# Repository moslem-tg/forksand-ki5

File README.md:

# ki5 RISC-V PCB in KiCAD

The ki5 board is a KiCAD port of SiFive's HiFive Unleashed board for the
RISC-V processor.

First draft done for:

* Ethernet
* FMC Connector
* Power Supply
* USB to UART and JTAG
* Freedom U540 IO and Power
* DDR 4x8 32 bits
* DDR 4x8 32 bit and ECC
* Freedom U540 DDR and Chiplink
* First draft of the Board

It remains to finish and check power circuits for this list.

The second draft, release of the Board in progress.

(C) 2018, 2019, Fork Sand, Inc.

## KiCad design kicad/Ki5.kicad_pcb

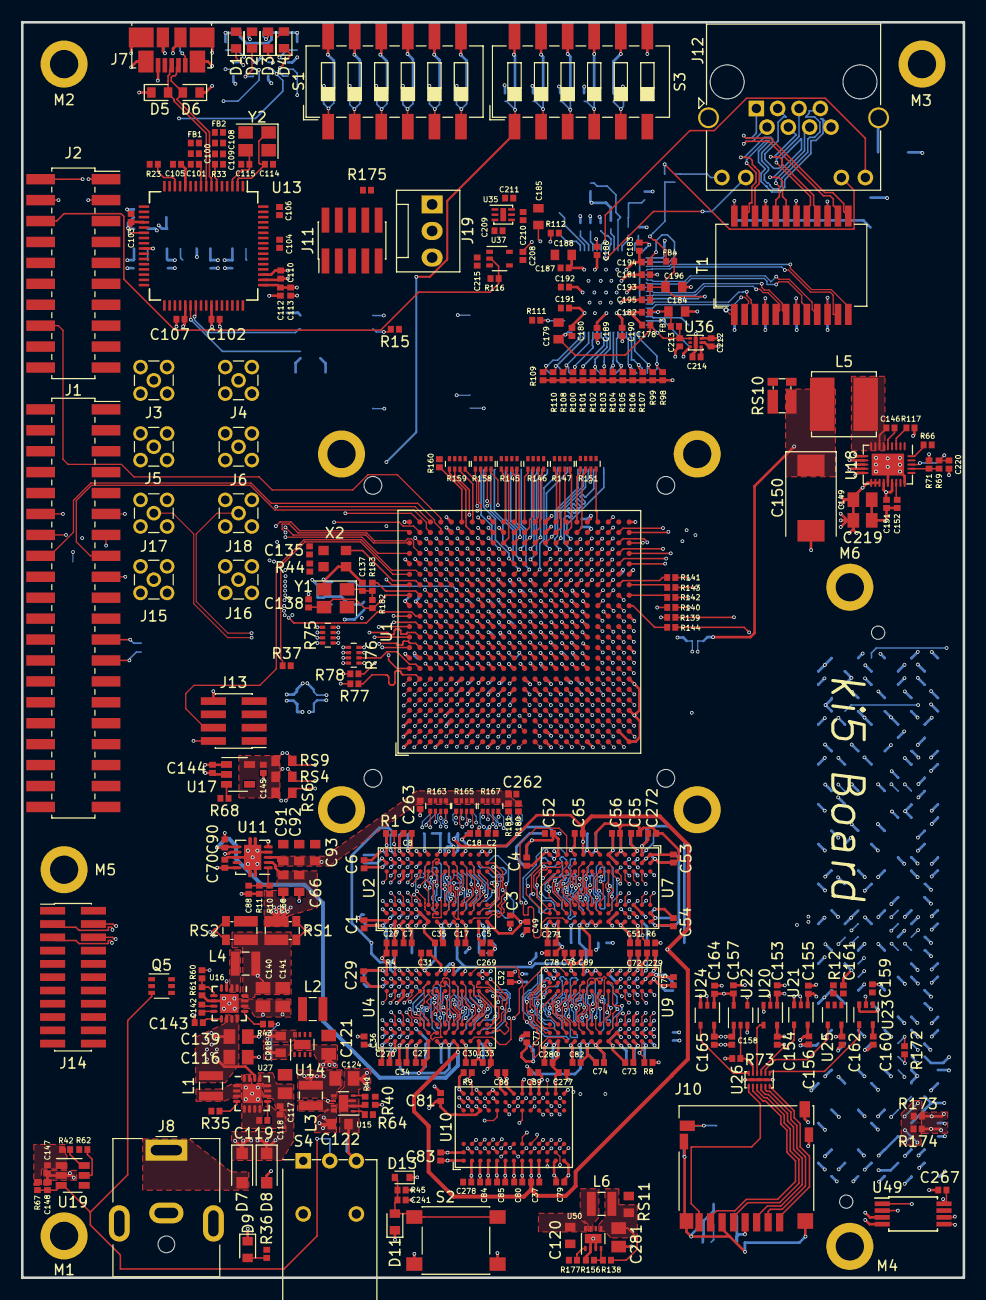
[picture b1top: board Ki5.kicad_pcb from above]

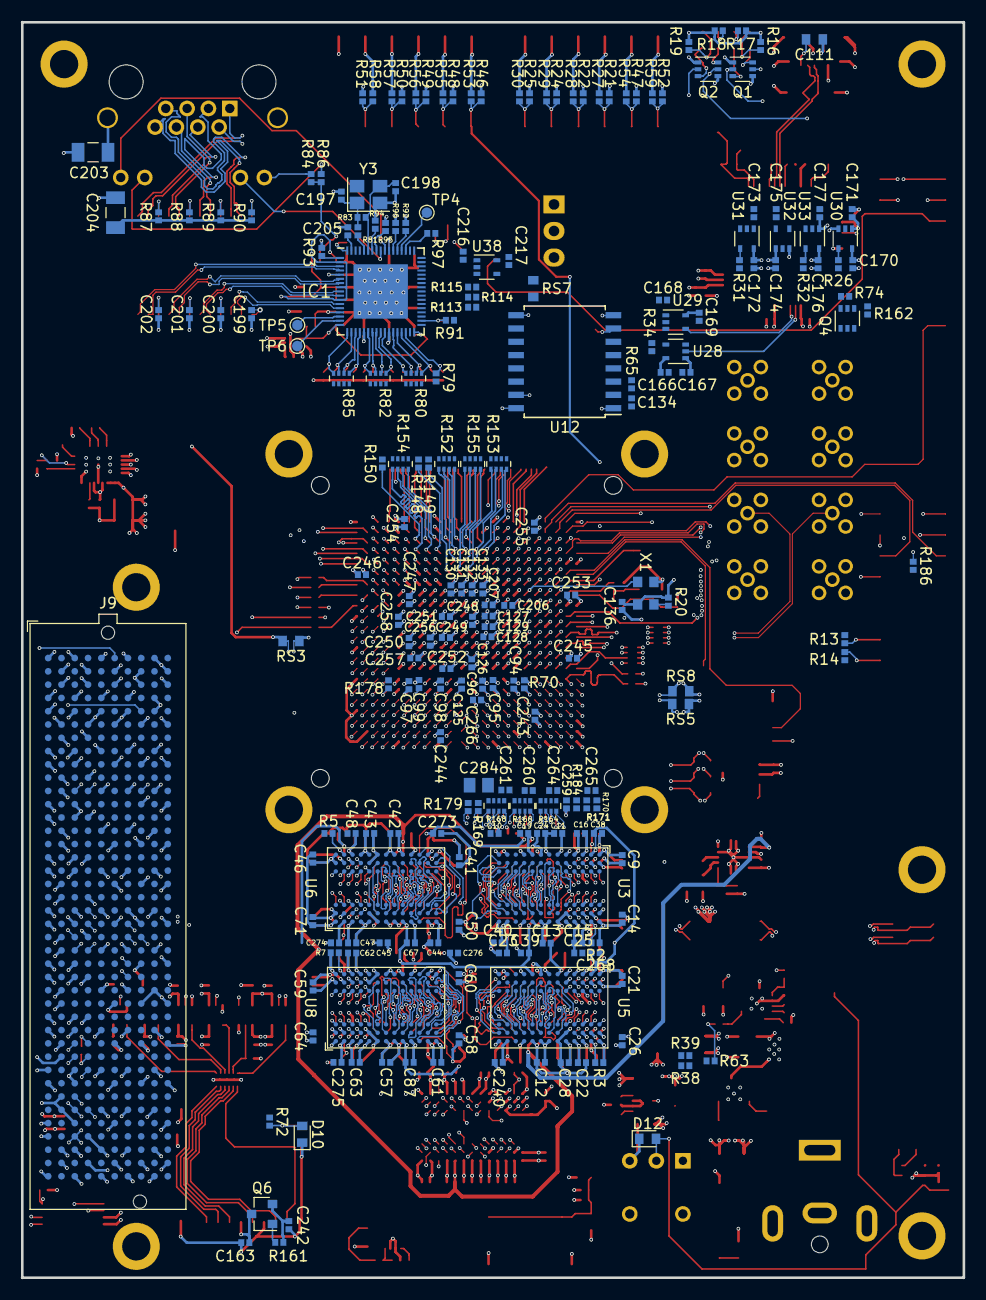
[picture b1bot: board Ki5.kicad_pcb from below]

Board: 10 copper layers, 90.0 x 120.0 mm, 542 parts (227 on the bottom side), 569 nets.

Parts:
C1, C6, C9, C14, C21, C26, C29, C34, C41, C46, C49, C54, C57, C62, C70, C71, C76, C79, C84, C94, C95, C96, C97, C100, C108, C112, C130, C131, C151, C163, C213, C243, C244, C245, C246, C247, C248, C249, C250, C251, C252: 4.7uF; C_0402_1005Metric
C2, C3, C4, C5, C7, C8, C10, C11, C12, C13, C15, C16, C17, C19, C22, C23, C24, C25, C27, C28, C30, C31, C32, C33, C35, C36, C37, C39, C42, C43, C44, C45, C47, C48, C50, C51, C52, C53, C55, C56, C58, C59, C60, C61, C63, C64, C65, C67, C69, C72, C73, C74, C75, C77, C78, C80, C81, C82, C83, C85, C86, C87, C89, C90, C98, C99, C101, C102, C103, C104, C105, C106, C107, C109, C110, C113, C118, C125, C126, C127, C129, C132, C133, C134, C135, C136, C146, C147, C153, C154, C155, C156, C157, C158, C159, C160, C161, C162, C164, C165, C166, C167, C168, C169, C170, C171, C172, C173, C174, C175, C176, C177, C178, C179, C181, C182, C183, C186, C188, C189, C190, C191, C192, C193, C194, C195, C199, C200, C201, C202, C206, C207, C208, C211, C214, C215, C216, C217, C220, C253, C254, C255, C256, C257, C258, C259, C260, C261, C262, C263, C264: 0.1uF; C_0402_1005Metric
C18, C20, C38, C40, C128, C144, C145, C209, C210, C212, C240, C242, C268, C269, C270, C271, C272, C273, C274, C275, C276, C277, C278, C279, C280: 1uF; C_0402_1005Metric
C66, C68, C91, C92, C93, C120, C122, C180, C184, C185, C187, C196, C218: 10uF; C_0603_1608Metric
C88: 1nF; C_0402_1005Metric
C111: 4.7uF; C_0603_1608Metric
C114, C115, C137, C138, C197, C198: 18pF; C_0402_1005Metric
C116, C121, C124, C139, C140, C141, C281: 22uF; C_0805_2012Metric
C117, C149, C219: 10uF; C_0805_2012Metric
C119: 33nF; C_0402_1005Metric
C142, C143, C148, C152, C205, C241, C265: 10nF; C_0402_1005Metric
C150: 220uF; CP_EIA-7343-20_Kemet-V
C203, C204: 1000pF, 2KV; C_1206_3216Metric
C266: 2.2pF; C_0402_1005Metric
C267: DNP; C_0402_1005Metric
C284: 0.1uF; C_0805_2012Metric
D1, D2, D3, D4, D9: Green; LED_0603_1608Metric
D5, D6, D10, D11, D12: PGB1010603NRHF; D_0603_1608Metric
D7: DB2W40300L; D_SOD-123F
D8: SMF12A; D_SOD-123F
D13: 1N4148WT; D_SOD-523
FB1, FB2, FB3, FB4: 120R; L_0402_1005Metric
IC1: VSC8541XMV-01; QFN-68-1EP_8x8mm_P0.4mm_EP5.2x5.2mm
J1: Conn_02x20_Odd_Even; PinSocket_2x20_P2.00mm_Vertical_SMD
J2: Conn_02x10_Odd_Even; PinSocket_2x10_P2.00mm_Vertical_SMD
J3, J4, J5, J6, J15, J16, J17, J18: Conn_Coaxial; MMCX_Molex_73415-1471_Vertical
J7: USB_B_Micro; USB_Micro-B_Molex_47346-0001
J8: Jack-DC; BarrelJack_CUI_PJ-063AH_Horizontal
J9: ASP-134602-01; Samtec_FMC_ASP-134602-01_10x40_P1.27mm_Vertical
J10: Micro_SD_Card_Det; microSD_HC_Hirose_DM3D-SF
J11: Conn_02x05_Odd_Even; PinHeader_2x05_P1.27mm_Vertical_SMD
J12: RJHSE5384; RJ45_Amphenol_RJHSE538X
J13: Conn_02x04_Odd_Even; PinHeader_2x04_P1.27mm_Vertical_SMD
J14: Conn_02x11_Odd_Even; PinHeader_2x11_P1.27mm_Vertical_SMD
J19: Fan_Tacho; FanPinHeader_1x03_P2.54mm_Vertical
L1: 1.0uH; L_Wuerth_MAPI-2512
L2, L3, L6: 2.2uH; L_Wuerth_MAPI-2512
L4: 0.47uH; L_Wuerth_MAPI-2510
L5: 1.0uH; L_Bourns_SRN6045TA
M1, M2, M3, M4, M5, M6: Mounting_Hole_PAD; MountingHole_2.7mm_M2.5_ISO7380_Pad
Q1, Q2, Q4, Q5: FDG6335N; SOT-363_SC-70-6
Q6: IRLML6402; SOT-23
R1, R2, R3, R4, R5, R6, R7, R8, R9, R70: 240R; R_0402_1005Metric
R10, R11, R107, R109, R111, R115: 10K; R_0402_1005Metric
R12, R20, R37, R40, R42, R44, R45, R62, R67, R69, R72, R74, R116, R161, R162: 100K; R_0402_1005Metric
R13, R14, R93: 2K; R_0402_1005Metric
R15: 47K; R_0402_1005Metric
R16, R17, R18, R19, R36, R84, R86: 330R; R_0402_1005Metric
R21, R22, R24, R25, R47, R52, R53, R55, R56, R57, R58, R73, R96, R113, R114: 4.7K; R_0402_1005Metric
R23, R33: 12K; R_0402_1005Metric
R26, R31, R32, R34: 1K; R_0402_1005Metric
R27, R28, R29, R30, R35, R46, R48, R49, R50, R51, R54, R59, R97, R98, R99, R100, R101, R102, R103, R104, R105, R106, R108, R110, R112: DNP; R_0402_1005Metric
R38: 210K; R_0402_1005Metric
R39, R41, R156: 33.2K; R_0402_1005Metric
R43, R63, R64, R65, R66, R68, R92, R94, R95, R117, R172, R173, R174, R175, R177, R183, R186: 0R; R_0402_1005Metric
R60: 80.6K; R_0402_1005Metric
R61: 160K; R_0402_1005Metric
R71: 82K; R_0402_1005Metric
R75, R76, R80, R82, R85, R145, R146, R147, R151, R152, R153, R154, R155, R158, R159: 33R; R_Array_Concave_4x0402
R77, R78, R79, R91, R139, R140, R141, R142, R143, R144, R148, R149, R150, R160: 33R; R_0402_1005Metric
R81: 39R; R_0402_1005Metric
R83, R182: 1M; R_0402_1005Metric
R87, R88, R89, R90, R178: 75R; R_0402_1005Metric
R138: 154K; R_0402_1005Metric
R163, R164, R165, R166, R167, R168: 49R9; R_Array_Convex_4x0402
R169, R170, R171, R179, R180, R181, R184: 49R9; R_0402_1005Metric
RS1, RS2, RS10: 0R001; R_Shunt_Vishay_WSKW0612
RS3, RS4, RS5, RS6, RS7, RS8, RS9: 0R20; R_0603_1608Metric
RS11: 0R02; R_0603_1608Metric
S1: SW DIP-6; SW_DIP_SPSTx06_Slide_6.7x16.8mm_W8.61mm_P2.54mm_LowProfile
S2: SW_Push; SW_SPST_PTS645
S3: DNP; SW_DIP_SPSTx06_Slide_6.7x16.8mm_W8.61mm_P2.54mm_LowProfile
S4: SW_Push_SPDT; SW_NKK_BB15AH
T1: TG111-MSC13LF; Transformer_Ethernet_HALO_TG111-MSC13
TP4, TP5, TP6: Test_Point; TestPoint_Pad_D1.0mm
U1: FU540-C000; BGA-484_23.0x23.0mm_Layout22x22_P1.0mm
U2, U3, U4, U5, U6, U7, U8, U9, U10: H5AN8G8NAFR-UH; FBGA-78_7.5x11mm_Layout2x3x13_P0.8mm
U11: TPS51200DRC; Texas_S-PVSON-N10
U12: IS25WP256D; SOIC-16W_7.5x10.3mm_P1.27mm
U13: FT2232HL; LQFP-64_10x10mm_P0.5mm
U14, U50: TLV62080DSGx; WSON-8-1EP_2x2mm_P0.5mm_EP0.9x1.6mm
U15: TLV62084DSGx; WSON-8-1EP_2x2mm_P0.5mm_EP0.9x1.6mm
U16: TLV62095RGTR; QFN-16-1EP_3x3mm_P0.5mm_EP1.8x1.8mm
U17: LP5907MFX-1.8/NOPB; SOT-23-5
U18: TPS51363; Texas_R-VFQFN-28-1EP_3.5x4.5mm_P0.4mm_EP2.1x3.1mm
U19: LM3880MFE-1AA/NOPB; SOT-23-6
U20, U21, U22, U23, U24, U25, U28, U29, U30, U31, U32, U33, U37, U38: SN74AUP1T34DCKR; SOT-353_SC-70-5
U26: TPD6F003; Texas_R-PWSON-N12_EP0.4x2mm
U27: TPS62133RGTT; QFN-16-1EP_3x3mm_P0.5mm_EP1.8x1.8mm
U35: MIC5353-2.5YMT-TR; MLF-6-1EP_1.6x1.6mm_P0.5mm_EP0.5x1.26mm
U36: NCP133AMX100TCG; DFN-6-1EP_1.2x1.2mm_P0.4mm_EP0.3x0.94mm
U49: M24C02-WMN; TSSOP-8_4.4x3mm_P0.65mm
X1: 33.3333 MHz; Oscillator_SMD_EuroQuartz_XO32-4Pin_3.2x2.5mm
X2: 1.0 MHz; Oscillator_SMD_EuroQuartz_XO32-4Pin_3.2x2.5mm
Y1: 33.333 MHz; Crystal_SMD_3225-4Pin_3.2x2.5mm
Y2: 12 MHz; Crystal_SMD_Abracon_ABM8G-4Pin_3.2x2.5mm
Y3: 25 MHz; Crystal_SMD_SeikoEpson_FA238-4Pin_3.2x2.5mm

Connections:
+1V0: C178.1, C179.1, C180.2, C213.1, FB3.1, IC1.17, IC1.34, U36.1
+1V2: C1.2, C2.2, C3.2, C4.2, C5.2, C6.2, C7.2, C8.2, C9.2, C10.2, C11.2, C12.2, C13.2, C14.2, C15.2, C16.2, C21.2, C22.2, C23.2, C24.2, C25.2, C26.2, C27.2, C28.2, C29.2, C30.2, C31.2, C32.2, C33.2, C34.2, C35.2, C36.2, C41.2, C42.2, C43.2, C44.1, C45.2, C46.2, C47.2, C48.2, C49.2, C50.2, C51.2, C52.2, C53.2, C54.2, C55.2, C56.2, C57.2, C58.2, C59.2, C60.2, C61.2, C62.2, C63.2, C64.2, C66.2, C68.2, C71.2, C72.2, C73.2, C74.2, C75.2, C76.2, C77.2, C78.2, C79.2, C80.2, C81.2, C82.2, C83.2, C84.2, C85.2, C86.2, R10.1, RS1.1, U2.A1, U2.B2, U2.B8, U2.C1, U2.C7, U2.C9, U2.E2, U2.E8, U2.F1, U2.F9, U2.H1, U2.J9, U2.M1, U2.N9, U3.A1, U3.B2, U3.B8, U3.C1, U3.C7, U3.C9, U3.E2, U3.E8, U3.F1, U3.F9, U3.H1, U3.J9, U3.M1, U3.N9, U4.A1, U4.B2, U4.B8, U4.C1, U4.C7, U4.C9, U4.E2, U4.E8, U4.F1, U4.F9, U4.H1, U4.J9, U4.M1, U4.N9, U5.A1, U5.B2, U5.B8, U5.C1, U5.C7, U5.C9, U5.E2, U5.E8, U5.F1, U5.F9, U5.H1, U5.J9, U5.M1, U5.N9, U6.A1, U6.B2, U6.B8, U6.C1, U6.C7, U6.C9, U6.E2, U6.E8, U6.F1, U6.F9, U6.H1, U6.J9, U6.M1, U6.N9, U7.A1, U7.B2, U7.B8, U7.C1, U7.C7, U7.C9, U7.E2, U7.E8, U7.F1, U7.F9, U7.H1, U7.J9, U7.M1, U7.N9, U8.A1, U8.B2, U8.B8, U8.C1, U8.C7, U8.C9, U8.E2, U8.E8, U8.F1, U8.F9, U8.H1, U8.J9, U8.M1, U8.N9, U9.A1, U9.B2, U9.B8, U9.C1, U9.C7, U9.C9, U9.E2, U9.E8, U9.F1, U9.F9, U9.H1, U9.J9, U9.M1, U9.N9, U10.A1, U10.B2, U10.B8, U10.C1, U10.C7, U10.C9, U10.E2, U10.E8, U10.F1, U10.F9, U10.H1, U10.J9, U10.M1, U10.N9, U11.2
+2V5: C185.2, C186.1, C208.1, C210.2, C216.1, FB4.1, IC1.58, R84.2, R86.2, R112.1, U35.4, U37.5, U38.1
+3.3VA: C163.2, J10.4, Q6.3
+3.3VP: C267.2, J9.D32, U49.8
+3V3: C70.2, C102.2, C103.2, C104.2, C110.2, C121.2, C144.1, C154.1, C156.1, C158.1, C160.1, C162.1, C165.1, C167.2, C169.2, C171.2, C173.2, C175.2, C177.2, C209.2, C242.2, FB1.2, FB2.2, L2.2, Q6.2, R16.1, R17.1, R18.1, R19.1, R23.1, R36.2, R38.2, R73.1, R74.2, R161.2, U11.7, U11.10, U13.20, U13.31, U13.42, U13.50, U13.56, U14.5, U17.1, U20.5, U21.5, U22.1, U23.5, U24.5, U25.5, U28.1, U29.5, U30.1, U31.1, U32.5, U33.1, U35.1, U35.3
+5V: C116.2, C120.2, C122.2, C139.2, C147.2, C151.1, C214.1, C218.2, J1.3, L1.2, R35.2, R42.2, R62.2, R67.2, U14.8, U15.8, U16.3, U16.10, U16.11, U16.12, U18.18, U18.20, U19.1, U27.14, U36.4, U50.8
+12V: C117.2, C118.2, C149.2, C219.2, D7.1, D8.1, J1.4, J1.6, J19.2, R173.2, R174.2, U18.15, U18.16, U18.17, U27.10, U27.11, U27.12, U27.13
/DDR4_x8_32b_1/REFIN: C88.1, R10.2, R11.1, U11.1
/Ethernet/CLKOUT: IC1.54, R97.2, R112.2
/Ethernet/CLK_SQUELCH_IN: IC1.57, R96.1
/Ethernet/COL: IC1.18, R85.4, R98.2
/Ethernet/CRS: IC1.19, R85.3, R99.2
/Ethernet/ELED0: IC1.60, J12.10
/Ethernet/ELED1: IC1.59, J12.12
/Ethernet/FASTLINK_FAIL_2V5: IC1.52, U38.2
/Ethernet/GEMGXL_MDINT: IC1.51, R115.2
/Ethernet/GEMGXL_RST_2V5: IC1.53, U37.4
/Ethernet/MX1_N: J12.7, T1.22
/Ethernet/MX1_P: J12.8, T1.23
/Ethernet/MX2_N: J12.3, T1.19
/Ethernet/MX2_P: J12.6, T1.20
/Ethernet/MX3_N: J12.4, T1.16
/Ethernet/MX3_P: J12.5, T1.17
/Ethernet/MX4_N: J12.1, T1.13
/Ethernet/MX4_P: J12.2, T1.14
/Ethernet/P0_D0_N: IC1.12, T1.3
/Ethernet/P0_D0_P: IC1.13, T1.2
/Ethernet/P0_D1_N: IC1.9, T1.6
/Ethernet/P0_D1_P: IC1.10, T1.5
/Ethernet/P0_D2_N: IC1.6, T1.9
/Ethernet/P0_D2_P: IC1.7, T1.8
/Ethernet/P0_D3_N: IC1.3, T1.12
/Ethernet/P0_D3_P: IC1.4, T1.11
/Ethernet/RXD0: IC1.29, R80.3, R100.2
/Ethernet/RXD1: IC1.27, R80.4, R101.2
/Ethernet/RXD2: IC1.26, R82.1, R102.2
/Ethernet/RXD3: IC1.25, R82.2, R103.2
/Ethernet/RXD4: IC1.24, R82.3, R104.2
/Ethernet/RXD5: IC1.23, R82.4, R105.2
/Ethernet/RXD6: IC1.21, R85.1, R106.2
/Ethernet/RXD7: IC1.20, R85.2, R107.2
/Ethernet/RX_CLK: IC1.32, R79.1, R109.2
/Ethernet/RX_DV: IC1.30, R80.2, R108.2
/Ethernet/RX_ER: IC1.31, R80.1, R110.2
/Ethernet/TX_CLK: IC1.36, R91.1, R111.2
/FMC.sch/FMC_GA0: J9.C34, U49.1
/FMC.sch/FMC_GA1: J9.D35, U49.2
/FMC.sch/FMC_SCL: J9.C30, U49.6
/FMC.sch/FMC_SDA: J9.C31, U49.5
/FT2232/FT_JTAG_SRST: Q4.6, R74.1, U13.22
/FT2232/FT_JTAG_TCK: U13.16, U30.2
/FT2232/FT_JTAG_TDI: U13.17, U31.2
/FT2232/FT_JTAG_TDO: U13.18, U32.4
/FT2232/FT_JTAG_TMS: U13.19, U33.2
/FT2232/FT_UART_RX: U13.39, U29.4
/FT2232/FT_UART_TX: U13.38, U28.2
/FT2232/USB_D_N: D6.2, J7.2, U13.7
/FT2232/USB_D_P: D5.2, J7.3, U13.8
/FT2232/VPHY_FT: C108.2, C109.2, FB2.1, U13.4
/FT2232/VPLL_FT: C100.2, C101.2, FB1.1, U13.9
/Freedom-U540_1/CHIPLINK_TX_CLK_R: R148.2, U1.P19
/Freedom-U540_1/CHIPLINK_TX_DAT0_R: R154.1, U1.T19
/Freedom-U540_1/CHIPLINK_TX_DAT1_R: R154.3, U1.R19
/Freedom-U540_1/CHIPLINK_TX_DAT2_R: R152.2, U1.N18
/Freedom-U540_1/CHIPLINK_TX_DAT3_R: R154.2, U1.R20
/Freedom-U540_1/CHIPLINK_TX_DAT4_R: R154.4, U1.P20
/Freedom-U540_1/CHIPLINK_TX_DAT5_R: R151.3, U1.U20
/Freedom-U540_1/CHIPLINK_TX_DAT6_R: R152.3, U1.N19
/Freedom-U540_1/CHIPLINK_TX_DAT7_R: R151.1, U1.U22
/Freedom-U540_1/CHIPLINK_TX_DAT8_R: R147.2, U1.R21
/Freedom-U540_1/CHIPLINK_TX_DAT9_R: R151.4, U1.W22
/Freedom-U540_1/CHIPLINK_TX_DAT10_R: R147.3, U1.T22
/Freedom-U540_1/CHIPLINK_TX_DAT11_R: R151.2, U1.U21
/Freedom-U540_1/CHIPLINK_TX_DAT12_R: R152.4, U1.M20
/Freedom-U540_1/CHIPLINK_TX_DAT13_R: R147.4, U1.T21
/Freedom-U540_1/CHIPLINK_TX_DAT14_R: R146.3, U1.N22
/Freedom-U540_1/CHIPLINK_TX_DAT15_R: R155.1, U1.M17
/Freedom-U540_1/CHIPLINK_TX_DAT16_R: R146.4, U1.N21
/Freedom-U540_1/CHIPLINK_TX_DAT17_R: R147.1, U1.R22
/Freedom-U540_1/CHIPLINK_TX_DAT18_R: R145.4, U1.L21
/Freedom-U540_1/CHIPLINK_TX_DAT19_R: R155.4, U1.M18
/Freedom-U540_1/CHIPLINK_TX_DAT20_R: R155.3, U1.L20
/Freedom-U540_1/CHIPLINK_TX_DAT21_R: R152.1, U1.N20
/Freedom-U540_1/CHIPLINK_TX_DAT22_R: R146.1, U1.M22
/Freedom-U540_1/CHIPLINK_TX_DAT23_R: R155.2, U1.M19
/Freedom-U540_1/CHIPLINK_TX_DAT24_R: R145.2, U1.K20
/Freedom-U540_1/CHIPLINK_TX_DAT25_R: R146.2, U1.M21
/Freedom-U540_1/CHIPLINK_TX_DAT26_R: R145.1, U1.K22
/Freedom-U540_1/CHIPLINK_TX_DAT27_R: R153.2, U1.L19
/Freedom-U540_1/CHIPLINK_TX_DAT28_R: R153.4, U1.K19
/Freedom-U540_1/CHIPLINK_TX_DAT29_R: R145.3, U1.L22
/Freedom-U540_1/CHIPLINK_TX_DAT30_R: R153.3, U1.L18
/Freedom-U540_1/CHIPLINK_TX_DAT31_R: R153.1, U1.L17
/Freedom-U540_1/CHIPLINK_TX_RST_R: R150.2, U1.T20
/Freedom-U540_1/CHIPLINK_TX_SEND_R: R149.2, U1.N17
/Freedom-U540_1/GEMGXL_TXD0_R: R75.8, U1.B12
/Freedom-U540_1/GEMGXL_TXD1_R: R75.7, U1.C11
/Freedom-U540_1/GEMGXL_TXD2_R: R75.6, U1.D11
/Freedom-U540_1/GEMGXL_TXD3_R: R75.5, U1.F11
/Freedom-U540_1/GEMGXL_TXD4_R: R76.8, U1.C10
/Freedom-U540_1/GEMGXL_TXD5_R: R76.7, U1.D10
/Freedom-U540_1/GEMGXL_TXD6_R: R76.6, U1.B8
/Freedom-U540_1/GEMGXL_TXD7_R: R76.5, U1.D9
/Freedom-U540_1/GEMGXL_TX_EN_R: R77.1, U1.B7
/Freedom-U540_1/GEMGXL_TX_ER_R: R78.1, U1.F10
/Freedom-U540_1/IO_DDR_RSVD0: J15.1, U1.E8
/Freedom-U540_1/IO_DDR_RSVD1: J16.1, U1.D8
/Freedom-U540_1/IO_DDR_RSVD2: J17.1, U1.F8
/Freedom-U540_1/IO_DDR_RSVD3: J18.1, U1.F9
/Freedom-U540_2/EN_VDD_SD: J2.10, Q4.5, R162.2, U1.B22
/Freedom-U540_2/GPIO0: J1.17, U1.F17
/Freedom-U540_2/GPIO1: J1.18, U1.C22
/Freedom-U540_2/GPIO2: J1.15, U1.C21
/Freedom-U540_2/GPIO3: J1.16, U1.D21
/Freedom-U540_2/GPIO4: J1.13, U1.E18
/Freedom-U540_2/GPIO5: J1.14, U1.D20
/Freedom-U540_2/GPIO6: J1.11, U1.E20
/Freedom-U540_2/GPIO7: J1.12, U1.C20
/Freedom-U540_2/GPIO8: J1.9, U1.D19
/Freedom-U540_2/GPIO9: J1.10, U1.A21
/Freedom-U540_2/GPIO10: R186.1, U1.F18
/Freedom-U540_2/GPIO15: J1.7, U1.G17
/Freedom-U540_2/HFXCLKIN: U1.F15, X1.3
/Freedom-U540_2/HFXSEL: R52.2, R59.1, S1.1, U1.C15
/Freedom-U540_2/I2C0_SCL: J1.25, R14.2, U1.Y14
/Freedom-U540_2/I2C0_SDA: J1.23, R13.2, U1.W13
/Freedom-U540_2/IO_PRCI_RSVD0: R46.2, R53.1, S3.1, U1.A16
/Freedom-U540_2/IO_PRCI_RSVD1: R48.2, R55.1, S3.2, U1.D13
/Freedom-U540_2/IO_PRCI_RSVD2: J3.1, U1.E13
/Freedom-U540_2/IO_PRCI_RSVD3: J13.1, U1.D16
/Freedom-U540_2/IO_PRCI_RSVD4: J13.2, U1.C16
/Freedom-U540_2/IO_PRCI_RSVD5: J13.3, U1.E15
/Freedom-U540_2/IO_PRCI_RSVD6: J13.4, U1.B17
/Freedom-U540_2/IO_PRCI_RSVD7: J13.5, U1.G13
/Freedom-U540_2/IO_PRCI_RSVD8: J13.6, U1.H13
/Freedom-U540_2/IO_PRCI_RSVD9: J13.7, U1.E16
/Freedom-U540_2/IO_PRCI_RSVD10: R49.2, R56.1, S3.3, U1.D17
/Freedom-U540_2/IO_PRCI_RSVD11: R51.2, R58.1, S3.5, U1.D14
/Freedom-U540_2/IO_PRCI_RSVD12: R50.2, R57.1, S3.4, U1.E14
/Freedom-U540_2/IO_PRCI_RSVD13: J4.1, U1.F14
/Freedom-U540_2/IO_PRCI_RSVD14: J5.1, U1.F13
/Freedom-U540_2/IO_PRCI_RSVD15: J6.1, U1.C14
/Freedom-U540_2/MSEL0: R21.2, R27.1, S1.3, U1.A19
/Freedom-U540_2/MSEL1: R22.2, R28.1, S1.4, U1.C18
/Freedom-U540_2/MSEL2: R24.2, R29.1, S1.5, U1.A20
/Freedom-U540_2/MSEL3: R25.2, R30.1, S1.6, U1.B19
/Freedom-U540_2/PWM0_0: J2.2, Q1.2, U1.G19
/Freedom-U540_2/PWM0_1: J2.4, Q1.5, U1.F21
/Freedom-U540_2/PWM0_2: J2.1, Q2.2, U1.F20
/Freedom-U540_2/PWM0_3: J2.3, Q2.5, U1.G20
/Freedom-U540_2/PWM1_0: J2.16, U1.D22
/Freedom-U540_2/PWM1_1: J2.18, U1.H17
/Freedom-U540_2/PWM1_2: J2.17, U1.G18
/Freedom-U540_2/PWM1_3: J2.19, U1.F19
/Freedom-U540_2/QSPI0_CS: R15.2, U1.J19, U12.7
/Freedom-U540_2/QSPI0_DQ0: U1.H21, U12.15
/Freedom-U540_2/QSPI0_DQ1: U1.H22, U12.8
/Freedom-U540_2/QSPI0_DQ2: U1.J21, U12.9
/Freedom-U540_2/QSPI0_DQ3: U1.H20, U12.1
/Freedom-U540_2/QSPI0_SCK: U1.K18, U12.16
/Freedom-U540_2/QSPI1_CS0: R158.4, U1.K17
/Freedom-U540_2/QSPI1_CS0_R: J1.30, R158.5
/Freedom-U540_2/QSPI1_CS1: R159.1, U1.G21
/Freedom-U540_2/QSPI1_CS1_R: J2.9, R159.8
/Freedom-U540_2/QSPI1_CS2: R159.4, U1.H19
/Freedom-U540_2/QSPI1_CS2_R: J2.11, R159.5
/Freedom-U540_2/QSPI1_CS3: R158.2, U1.J20
/Freedom-U540_2/QSPI1_CS3_R: J2.13, R158.7
/Freedom-U540_2/QSPI1_DQ0: R159.3, U1.G22
/Freedom-U540_2/QSPI1_DQ0_R: J1.28, R159.6
/Freedom-U540_2/QSPI1_DQ1: R158.1, U1.J18
/Freedom-U540_2/QSPI1_DQ1_R: J1.32, R158.8
/Freedom-U540_2/QSPI1_DQ2: R160.2, U1.F22
/Freedom-U540_2/QSPI1_DQ2_R: J2.5, R160.1
/Freedom-U540_2/QSPI1_DQ3: R158.3, U1.J17
/Freedom-U540_2/QSPI1_DQ3_R: J2.7, R158.6
/Freedom-U540_2/QSPI1_SCK: R159.2, U1.H18
/Freedom-U540_2/QSPI1_SCK_R: J1.34, R159.7
/Freedom-U540_2/QSPI2_CS: R144.2, U1.AB14
/Freedom-U540_2/QSPI2_CS_3V3: U25.4, U26.2
/Freedom-U540_2/QSPI2_CS_CON: J10.2, U26.11
/Freedom-U540_2/QSPI2_CS_R: R12.1, R144.1, U25.2
/Freedom-U540_2/QSPI2_HOLD: R140.2, U1.Y15
/Freedom-U540_2/QSPI2_HOLD_3V3: U24.4, U26.6
/Freedom-U540_2/QSPI2_HOLD_CON: J10.8, U26.7
/Freedom-U540_2/QSPI2_HOLD_R: R140.1, U24.2
/Freedom-U540_2/QSPI2_MISO: R142.2, U1.AB15
/Freedom-U540_2/QSPI2_MISO_3V3: R73.2, U22.2, U26.5
/Freedom-U540_2/QSPI2_MISO_CON: J10.7, U26.8
/Freedom-U540_2/QSPI2_MISO_R: R142.1, U22.4
/Freedom-U540_2/QSPI2_MOSI: R141.2, U1.AA16
/Freedom-U540_2/QSPI2_MOSI_3V3: U21.4, U26.3
/Freedom-U540_2/QSPI2_MOSI_CON: J10.3, U26.10
/Freedom-U540_2/QSPI2_MOSI_R: R141.1, U21.2
/Freedom-U540_2/QSPI2_SCK: R139.2, U1.W15
/Freedom-U540_2/QSPI2_SCK_3V3: U20.4, U26.4
/Freedom-U540_2/QSPI2_SCK_CON: J10.5, U26.9
/Freedom-U540_2/QSPI2_SCK_R: R139.1, U20.2
/Freedom-U540_2/QSPI2_WP: R143.2, U1.AB16
/Freedom-U540_2/QSPI2_WP_3V3: U23.4, U26.1
/Freedom-U540_2/QSPI2_WP_CON: J10.1, U26.12
/Freedom-U540_2/QSPI2_WP_R: R143.1, U23.2
/Freedom-U540_2/RTCXALTCLKIN: U1.B16, X2.3
/Freedom-U540_2/RTCXSEL: R47.2, R54.1, S1.2, U1.D15
/Freedom-U540_2/SD_CD: D10.2, J2.12, J10.9, R72.1, U1.B20
/Freedom-U540_2/UART1_RX: J1.27, U1.AA14
/Freedom-U540_2/UART1_TX: J1.29, U1.AA15
/Power.sch/EN_1V8: R64.1, U15.1
/Power.sch/EN_3V3: R63.1, U14.1
/Power.sch/EN_CORE: R66.1, U18.28
/Power.sch/EN_DDR: R43.1, U16.13
/Power.sch/EN_DDR_VPP: R177.1, U50.1
/Power.sch/EN_PLL: R68.1, U17.3
/Power.sch/PWR_EN1: R42.1, R43.2, R63.2, R64.2, R177.2, U19.6
/Power.sch/PWR_EN2: R62.1, R66.2, R68.2, U19.5
/Power.sch/PWR_ON: C148.2, D12.2, Q5.3, R67.1, S4.2, U19.3
AGND: C1.1, C2.1, C3.1, C4.1, C5.1, C6.1, C7.1, C8.1, C9.1, C10.1, C11.1, C12.1, C13.1, C14.1, C15.1, C16.1, C17.1, C18.1, C19.1, C20.1, C21.1, C22.1, C23.1, C24.1, C25.1, C26.1, C27.1, C28.1, C29.1, C30.1, C31.1, C32.1, C33.1, C34.1, C35.1, C36.1, C37.1, C38.1, C39.1, C40.1, C41.1, C42.1, C43.1, C44.2, C45.1, C46.1, C47.1, C48.1, C49.1, C50.1, C51.1, C52.1, C53.1, C54.1, C55.1, C56.1, C57.1, C58.1, C59.1, C60.1, C61.1, C62.1, C63.1, C64.1, C65.1, C66.1, C67.1, C68.1, C69.1, C70.1, C71.1, C72.1, C73.1, C74.1, C75.1, C76.1, C77.1, C78.1, C79.1, C80.1, C81.1, C82.1, C83.1, C84.1, C85.1, C86.1, C87.1, C88.2, C89.1, C90.1, C91.1, C92.1, C93.1, C94.2, C95.2, C96.2, C97.2, C98.2, C99.2, C100.1, C101.1, C102.1, C103.1, C104.1, C105.1, C106.1, C107.1, C108.1, C109.1, C110.1, C111.1, C112.1, C113.1, C114.1, C115.1, C116.1, C117.1, C118.1, C119.1, C120.1, C121.1, C122.1, C124.1, C125.2, C126.2, C127.2, C128.2, C129.2, C130.2, C131.2, C132.2, C133.2, C134.1, C135.1, C136.1, C137.1, C138.1, C139.1, C140.1, C141.1, C143.2, C144.2, C145.2, C147.1, C148.1, C149.1, C150.2, C151.2, C152.1, C153.2, C154.2, C155.2, C156.2, C157.2, C158.2, C159.2, C160.2, C161.2, C162.2, C163.1, C164.2, C165.2, C166.1, C167.1, C168.1, C169.1, C170.1, C171.1, C172.1, C173.1, C174.1, C175.1, C176.1, C177.1, C178.2, C179.2, C180.1, C181.2, C182.2, C183.2, C184.1, C185.1, C186.2, C187.1, C188.2, C189.2, C190.2, C191.2, C192.2, C193.2, C194.2, C195.2, C196.1, C197.1, C198.1, C199.1, C200.1, C201.1, C202.1, C203.1, C203.2, C204.1, C205.2, C206.1, C207.1, C208.2, C209.1, C210.1, C211.1, C212.1, C213.2, C214.2, C215.2, C216.2, C217.2, C218.1, C219.1, C220.1, C240.1, C241.2, C242.1, C243.2, C244.2, C245.2, C246.2, C247.2, C248.2, C249.2, C250.2, C251.2, C252.2, C253.2, C254.2, C255.2, C256.2, C257.2, C258.2, C259.1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
AVDD_DDRPLL_N: C127.1, J14.16, RS4.2, U1.K13
AVDD_DDRPLL_P: C145.1, J14.7, J14.15, J14.19, RS4.1, RS6.2, RS9.1, U17.5
CHIPLINK_RX_CLK: J9.G2, U1.AA22
CHIPLINK_RX_DAT0: J9.D20, U1.Y16
CHIPLINK_RX_DAT1: J9.D21, U1.AB18
CHIPLINK_RX_DAT2: J9.C22, U1.AA18
CHIPLINK_RX_DAT3: J9.C23, U1.W17
CHIPLINK_RX_DAT4: J9.H22, U1.W16
CHIPLINK_RX_DAT5: J9.H23, U1.W18
CHIPLINK_RX_DAT6: J9.G21, U1.Y18
CHIPLINK_RX_DAT7: J9.G22, U1.Y17
CHIPLINK_RX_DAT8: J9.H25, U1.AA19
CHIPLINK_RX_DAT9: J9.H26, U1.V18
CHIPLINK_RX_DAT10: J9.G24, U1.Y19
CHIPLINK_RX_DAT11: J9.G25, U1.W19
CHIPLINK_RX_DAT12: J9.D23, U1.V16
CHIPLINK_RX_DAT13: J9.D24, U1.AB19
CHIPLINK_RX_DAT14: J9.H28, U1.U18
CHIPLINK_RX_DAT15: J9.H29, U1.V19
CHIPLINK_RX_DAT16: J9.G27, U1.V17
CHIPLINK_RX_DAT17: J9.G28, U1.R18
CHIPLINK_RX_DAT18: J9.D26, U1.U19
CHIPLINK_RX_DAT19: J9.D27, U1.T18
CHIPLINK_RX_DAT20: J9.C26, U1.U17
CHIPLINK_RX_DAT21: J9.C27, U1.P18
CHIPLINK_RX_DAT22: J9.H31, U1.AB20
CHIPLINK_RX_DAT23: J9.H32, U1.AA20
CHIPLINK_RX_DAT24: J9.G30, U1.R17
CHIPLINK_RX_DAT25: J9.G31, U1.V20
CHIPLINK_RX_DAT26: J9.H34, U1.AB21
CHIPLINK_RX_DAT27: J9.H35, U1.Y20
CHIPLINK_RX_DAT28: J9.G33, U1.W20
CHIPLINK_RX_DAT29: J9.G34, U1.AA21
CHIPLINK_RX_DAT30: J9.H37, U1.Y22
CHIPLINK_RX_DAT31: J9.H38, U1.Y21
CHIPLINK_RX_RST: J9.G37, U1.P17
CHIPLINK_RX_SEND: J9.G36, U1.W21
CHIPLINK_TX_CLK: J9.H4, R148.1
CHIPLINK_TX_DAT0: J9.G6, R154.8
CHIPLINK_TX_DAT1: J9.G7, R154.6
CHIPLINK_TX_DAT2: J9.D8, R152.7
CHIPLINK_TX_DAT3: J9.D9, R154.7
CHIPLINK_TX_DAT4: J9.H7, R154.5
CHIPLINK_TX_DAT5: J9.H8, R151.6
CHIPLINK_TX_DAT6: J9.G9, R152.6
CHIPLINK_TX_DAT7: J9.G10, R151.8
CHIPLINK_TX_DAT8: J9.H10, R147.7
CHIPLINK_TX_DAT9: J9.H11, R151.5
CHIPLINK_TX_DAT10: J9.D11, R147.6
CHIPLINK_TX_DAT11: J9.D12, R151.7
CHIPLINK_TX_DAT12: J9.C10, R152.5
CHIPLINK_TX_DAT13: J9.C11, R147.5
CHIPLINK_TX_DAT14: J9.H13, R146.6
CHIPLINK_TX_DAT15: J9.H14, R155.8
CHIPLINK_TX_DAT16: J9.G12, R146.5
CHIPLINK_TX_DAT17: J9.G13, R147.8
CHIPLINK_TX_DAT18: J9.D14, R145.5
CHIPLINK_TX_DAT19: J9.D15, R155.5
CHIPLINK_TX_DAT20: J9.C14, R155.6
CHIPLINK_TX_DAT21: J9.C15, R152.8
CHIPLINK_TX_DAT22: J9.H16, R146.8
CHIPLINK_TX_DAT23: J9.H17, R155.7
CHIPLINK_TX_DAT24: J9.G15, R145.7
CHIPLINK_TX_DAT25: J9.G16, R146.7
CHIPLINK_TX_DAT26: J9.D17, R145.8
CHIPLINK_TX_DAT27: J9.D18, R153.7
CHIPLINK_TX_DAT28: J9.C18, R153.5
CHIPLINK_TX_DAT29: J9.C19, R145.6
CHIPLINK_TX_DAT30: J9.H19, R153.6
CHIPLINK_TX_DAT31: J9.H20, R153.8
CHIPLINK_TX_RST: J9.G19, R150.1
CHIPLINK_TX_SEND: J9.G18, R149.1
DDR_A0: R167.3, U1.N3, U2.L3, U3.L3, U4.L3, U5.L3, U6.L3, U7.L3, U8.L3, U9.L3, U10.L3
DDR_A1: R168.4, U1.R1, U2.L7, U3.L7, U4.L7, U5.L7, U6.L7, U7.L7, U8.L7, U9.L7, U10.L7
DDR_A2: R181.2, U1.N4, U2.M3, U3.M3, U4.M3, U5.M3, U6.M3, U7.M3, U8.M3, U9.M3, U10.M3
DDR_A3: R166.2, U1.P3, U2.K7, U3.K7, U4.K7, U5.K7, U6.K7, U7.K7, U8.K7, U9.K7, U10.K7
DDR_A4: R167.1, U1.T1, U2.K3, U3.K3, U4.K3, U5.K3, U6.K3, U7.K3, U8.K3, U9.K3, U10.K3
DDR_A5: R168.3, U1.N5, U2.L8, U3.L8, U4.L8, U5.L8, U6.L8, U7.L8, U8.L8, U9.L8, U10.L8
DDR_A6: R167.2, U1.P4, U2.L2, U3.L2, U4.L2, U5.L2, U6.L2, U7.L2, U8.L2, U9.L2, U10.L2
DDR_A7: R168.1, U1.R2, U2.M8, U3.M8, U4.M8, U5.M8, U6.M8, U7.M8, U8.M8, U9.M8, U10.M8
DDR_A8: R167.4, U1.R3, U2.M2, U3.M2, U4.M2, U5.M2, U6.M2, U7.M2, U8.M2, U9.M2, U10.M2
DDR_A9: R168.2, U1.T3, U2.M7, U3.M7, U4.M7, U5.M7, U6.M7, U7.M7, U8.M7, U9.M7, U10.M7
DDR_A10: R165.3, U1.U1, U2.J3, U3.J3, U4.J3, U5.J3, U6.J3, U7.J3, U8.J3, U9.J3, U10.J3
DDR_A11: R180.2, U1.R4, U2.N2, U3.N2, U4.N2, U5.N2, U6.N2, U7.N2, U8.N2, U9.N2, U10.N2
DDR_A12: R166.4, U1.P5, U2.J7, U3.J7, U4.J7, U5.J7, U6.J7, U7.J7, U8.J7, U9.J7, U10.J7
DDR_A13: R169.2, U1.T2, U2.N8, U3.N8, U4.N8, U5.N8, U6.N8, U7.N8, U8.N8, U9.N8, U10.N8
DDR_ACT_N: R165.1, U1.U3, U2.H3, U3.H3, U4.H3, U5.H3, U6.H3, U7.H3, U8.H3, U9.H3, U10.H3
DDR_ALERT_N: R178.1, U1.W6, U2.L9, U3.L9, U4.L9, U5.L9, U6.L9, U7.L9, U8.L9, U9.L9, U10.L9
DDR_BA0: R165.4, U1.M4, U2.K2, U3.K2, U4.K2, U5.K2, U6.K2, U7.K2, U8.K2, U9.K2, U10.K2
DDR_BA1: R166.1, U1.N2, U2.K8, U3.K8, U4.K8, U5.K8, U6.K8, U7.K8, U8.K8, U9.K8, U10.K8
DDR_BG0: R165.2, U1.M5, U2.J2, U3.J2, U4.J2, U5.J2, U6.J2, U7.J2, U8.J2, U9.J2, U10.J2
DDR_BG1: R166.3, U1.V3, U2.J8, U3.J8, U4.J8, U5.J8, U6.J8, U7.J8, U8.J8, U9.J8, U10.J8
DDR_CAS_N: R164.2, U1.M3, U2.H7, U3.H7, U4.H7, U5.H7, U6.H7, U7.H7, U8.H7, U9.H7, U10.H7
DDR_CKE: R163.3, U1.AB6, U2.G3, U3.G3, U4.G3, U5.G3, U6.G3, U7.G3, U8.G3, U9.G3, U10.G3
DDR_CKE1: R163.2, U1.AA6, U2.G2, U3.G2, U4.G2, U5.G2, U6.G2, U7.G2, U8.G2, U9.G2, U10.G2
DDR_CLK_N: C266.2, R171.2, U1.L5, U2.F8, U3.F8, U4.F8, U5.F8, U6.F8, U7.F8, U8.F8, U9.F8, U10.F8
DDR_CLK_P: C266.1, R170.2, U1.K5, U2.F7, U3.F7, U4.F7, U5.F7, U6.F7, U7.F7, U8.F7, U9.F7, U10.F7
DDR_CS0_N: R164.4, U1.Y6, U2.G7, U3.G7, U4.G7, U5.G7, U6.G7, U7.G7, U8.G7, U9.G7, U10.G7
DDR_CS1_N: R164.3, U1.W7, U2.G8, U3.G8, U4.G8, U5.G8, U6.G8, U7.G8, U8.G8, U9.G8, U10.G8
DDR_DM0: U1.E5, U2.A7
DDR_DM1: U1.G5, U3.A7
DDR_DM2: U1.C6, U4.A7
DDR_DM3: U1.D5, U5.A7
DDR_DM4: U1.T5, U6.A7
DDR_DM5: U1.W5, U7.A7
DDR_DM6: U1.W10, U8.A7
DDR_DM7: U1.AB12, U9.A7
DDR_DQ0: U1.D2, U2.D3
DDR_DQ1: U1.B1, U2.D2
DDR_DQ2: U1.F4, U2.D8
DDR_DQ3: U1.E2, U2.E3
DDR_DQ4: U1.C1, U2.C2
DDR_DQ5: U1.G4, U2.E7
DDR_DQ6: U1.E1, U2.B7
DDR_DQ7: U1.G3, U2.D7
DDR_DQ8: U1.H4, U3.B7
DDR_DQ9: U1.F1, U3.E7
DDR_DQ10: U1.F5, U3.D8
DDR_DQ11: U1.G1, U3.D7
DDR_DQ12: U1.H1, U3.E3
DDR_DQ13: U1.J3, U3.D3
DDR_DQ14: U1.J2, U3.C2
DDR_DQ15: U1.J4, U3.D2
DDR_DQ16: U1.B4, U4.B7
DDR_DQ17: U1.B2, U4.E7
DDR_DQ18: U1.A4, U4.D7
DDR_DQ19: U1.A5, U4.D3
DDR_DQ20: U1.B5, U4.D8
DDR_DQ21: U1.C5, U4.C2
DDR_DQ22: U1.B3, U4.E3
DDR_DQ23: U1.B6, U4.D2
DDR_DQ24: U1.C4, U5.C2
DDR_DQ25: U1.D4, U5.D3
DDR_DQ26: U1.D6, U5.B7
DDR_DQ27: U1.C3, U5.D2
DDR_DQ28: U1.E6, U5.D8
DDR_DQ29: U1.C2, U5.E3
DDR_DQ30: U1.D3, U5.E7
DDR_DQ31: U1.C7, U5.D7
DDR_DQ32: U1.R5, U6.C2
DDR_DQ33: U1.W1, U6.D8
DDR_DQ34: U1.T4, U6.E7
DDR_DQ35: U1.V2, U6.E3
DDR_DQ36: U1.Y1, U6.B7
DDR_DQ37: U1.W3, U6.D7
DDR_DQ38: U1.W2, U6.D2
DDR_DQ39: U1.U5, U6.D3
DDR_DQ40: U1.V5, U7.C2
DDR_DQ41: U1.AA1, U7.D3
DDR_DQ42: U1.Y3, U7.E3
DDR_DQ43: U1.Y2, U7.D2
DDR_DQ44: U1.AB2, U7.E7
DDR_DQ45: U1.AA3, U7.B7
DDR_DQ46: U1.AB3, U7.D8
DDR_DQ47: U1.AA4, U7.D7
DDR_DQ48: U1.Y12, U8.E3
DDR_DQ49: U1.W11, U8.E7
DDR_DQ50: U1.Y11, U8.D2
DDR_DQ51: U1.W8, U8.D7
DDR_DQ52: U1.Y10, U8.C2
DDR_DQ53: U1.Y9, U8.D3
DDR_DQ54: U1.W12, U8.D8
DDR_DQ55: U1.W9, U8.B7
DDR_DQ56: U1.AA13, U9.E3
DDR_DQ57: U1.AB8, U9.C2
DDR_DQ58: U1.AA12, U9.D3
DDR_DQ59: U1.AB9, U9.D7
DDR_DQ60: U1.AB11, U9.D8
DDR_DQ61: U1.AA10, U9.E7
DDR_DQ62: U1.AA9, U9.B7
DDR_DQ63: U1.AA11, U9.D2
DDR_DQS0_N: U1.F3, U2.B3
DDR_DQS0_P: U1.F2, U2.C3
DDR_DQS1_N: U1.H3, U3.B3
DDR_DQS1_P: U1.H2, U3.C3
DDR_DQS2_N: U1.A7, U4.B3
DDR_DQS2_P: U1.A6, U4.C3
DDR_DQS3_N: U1.D7, U5.B3
DDR_DQS3_P: U1.E7, U5.C3
DDR_DQS4_N: U1.U4, U6.B3
DDR_DQS4_P: U1.V4, U6.C3
DDR_DQS5_N: U1.W4, U7.B3
DDR_DQS5_P: U1.Y4, U7.C3
DDR_DQS6_N: U1.AA7, U8.B3
DDR_DQS6_P: U1.Y7, U8.C3
DDR_DQS7_N: U1.Y8, U9.B3
DDR_DQS7_P: U1.AA8, U9.C3
DDR_ECC_DM: U1.J5, U10.A7
DDR_ECC_DQ0: U1.H5, U10.D2
DDR_ECC_DQ1: U1.K1, U10.E7
DDR_ECC_DQ2: U1.K4, U10.B7
DDR_ECC_DQ3: U1.L2, U10.D8
DDR_ECC_DQ4: U1.L1, U10.D3
DDR_ECC_DQ5: U1.L4, U10.C2
DDR_ECC_DQ6: U1.M1, U10.E3
DDR_ECC_DQ7: U1.L3, U10.D7
DDR_ECC_DQS_N: U1.K3, U10.B3
DDR_ECC_DQS_P: U1.K2, U10.C3
DDR_ODT: R163.1, U1.AA5, U2.F3, U3.F3, U4.F3, U5.F3, U6.F3, U7.F3, U8.F3, U9.F3, U10.F3
DDR_ODT1: R184.2, U1.AB5, U2.F2, U3.F2, U4.F2, U5.F2, U6.F2, U7.F2, U8.F2, U9.F2, U10.F2
DDR_PARITY_IN: R179.2, U1.U2, U2.N3, U3.N3, U4.N3, U5.N3, U6.N3, U7.N3, U8.N3, U9.N3, U10.N3
DDR_RAS_N: R164.1, U1.M2, U2.H8, U3.H8, U4.H8, U5.H8, U6.H8, U7.H8, U8.H8, U9.H8, U10.H8
DDR_RESET_N: U1.Y5, U2.L1, U3.L1, U4.L1, U5.L1, U6.L1, U7.L1, U8.L1, U9.L1, U10.L1
DDR_WE_N: R163.4, U1.N1, U2.H2, U3.H2, U4.H2, U5.H2, U6.H2, U7.H2, U8.H2, U9.H2, U10.H2
FASTLINK_FAIL: J2.8, U1.E19, U38.4
GEMGXL_GTX_CLK: IC1.37, R97.1, U1.E12
GEMGXL_MDC: IC1.48, R113.1, U1.B13
GEMGXL_MDIO: IC1.50, R114.2, U1.C12
GEMGXL_RST: J2.6, R116.2, U1.B21, U37.2
GEMGXL_RXD0: R80.6, U1.A12
GEMGXL_RXD1: R80.5, U1.B10
GEMGXL_RXD2: R82.8, U1.A10
GEMGXL_RXD3: R82.7, U1.E11
GEMGXL_RXD4: R82.6, U1.E10
GEMGXL_RXD5: R82.5, U1.A8
GEMGXL_RXD6: R85.8, U1.C9
GEMGXL_RXD7: R85.7, U1.E9
GEMGXL_RX_CLK: R79.2, U1.F12
GEMGXL_RX_COL: R85.5, U1.A13
GEMGXL_RX_CRS: R85.6, U1.C13
GEMGXL_RX_DV: R80.7, U1.A11
GEMGXL_RX_ER: R80.8, U1.B11
GEMGXL_TXD0: IC1.38, R75.1
GEMGXL_TXD1: IC1.40, R75.2
GEMGXL_TXD2: IC1.41, R75.3
GEMGXL_TXD3: IC1.42, R75.4
GEMGXL_TXD4: IC1.43, R76.1
GEMGXL_TXD5: IC1.45, R76.2
GEMGXL_TXD6: IC1.46, R76.3
GEMGXL_TXD7: IC1.47, R76.4
GEMGXL_TX_CLK: R91.2, U1.C8
GEMGXL_TX_EN: IC1.33, R77.2
GEMGXL_TX_ER: IC1.35, R78.2
JTAG_TCK: J11.1, R26.1, U1.D18
JTAG_TDI: J11.9, R31.1, U1.C19
JTAG_TDO: J11.3, U1.E17, U32.2
JTAG_TMS: J11.5, R32.1, U1.F16
unnamed: C111.2, J7.1
unnamed: C114.2, U13.2, Y2.1
unnamed: C115.2, U13.3, Y2.3
unnamed: C119.2, U27.9
unnamed: C137.2, R182.2, R183.1, Y1.1
unnamed: C138.2, R182.1, U1.A15, Y1.3
unnamed: C142.1, U16.7
unnamed: C142.2, U16.8
unnamed: C143.1, U16.9
unnamed: C146.1, L5.1, U18.6, U18.7, U18.8, U18.9
unnamed: C146.2, U18.5
unnamed: C152.2, U18.21
unnamed: C181.1, C182.1, C183.1, C184.2, FB3.2, IC1.5, IC1.14, IC1.68
unnamed: C193.1, C194.1, C195.1, C196.2, FB4.2, IC1.2, IC1.8, IC1.11
unnamed: C197.2, R81.1, R83.2, Y3.1
unnamed: C198.2, IC1.63, R83.1, Y3.3
unnamed: C199.2, T1.1
unnamed: C200.2, T1.4
unnamed: C201.2, T1.7
unnamed: C202.2, T1.10
unnamed: C204.2, R87.1, R88.1, R89.1, R90.1
unnamed: C205.1, IC1.67
unnamed: C211.2, U35.6
unnamed: C220.2, R69.2, U18.26
unnamed: C265.2, R170.1, R171.1
unnamed: D1.1, Q1.6
unnamed: D1.2, R16.2
unnamed: D2.1, Q1.3
unnamed: D2.2, R17.2
unnamed: D3.1, Q2.6
unnamed: D3.2, R18.2
unnamed: D4.1, Q2.3
unnamed: D4.2, R19.2
unnamed: D7.2, J8.1
unnamed: D9.2, R36.1
unnamed: IC1.1, R93.2
unnamed: IC1.15, TP5.1
unnamed: IC1.16, TP6.1
unnamed: IC1.55, TP4.1
unnamed: IC1.56, R92.1
unnamed: IC1.61, R95.1
unnamed: IC1.62, R94.1
unnamed: IC1.64, R81.2
unnamed: J9.C35, J9.C37, R173.1, R174.1
unnamed: J9.D30, R172.1
unnamed: J9.D31, R172.2
unnamed: J9.H5, R175.1
unnamed: J12.9, R84.1
unnamed: J12.11, R86.1
unnamed: L1.1, U27.1, U27.2, U27.3
unnamed: L2.1, U14.7
unnamed: L3.1, U15.7
unnamed: L4.1, U16.1, U16.2
unnamed: L6.1, U50.7
unnamed: Q4.3, Q6.1, R161.1
unnamed: R1.2, U2.B9
unnamed: R2.2, U3.B9
unnamed: R3.2, U5.B9
unnamed: R4.2, U4.B9
unnamed: R5.2, U6.B9
unnamed: R6.2, U7.B9
unnamed: R7.2, U8.B9
unnamed: R8.2, U9.B9
unnamed: R9.2, U10.B9
unnamed: R20.2, X1.1
unnamed: R23.2, U13.14
unnamed: R26.2, U30.4
unnamed: R31.2, U31.4
unnamed: R32.2, U33.4
unnamed: R33.2, U13.6
unnamed: R34.2, U28.4
unnamed: R35.1, U27.4
unnamed: R38.1, R39.1, U14.4
unnamed: R40.1, R41.1, U15.4
unnamed: R44.1, X2.1
unnamed: R60.1, R61.2, U16.5
unnamed: R65.2, U12.3
unnamed: R69.1, R71.2, U18.25
unnamed: R70.2, U1.F6
unnamed: R87.2, T1.15
unnamed: R88.2, T1.18
unnamed: R89.2, T1.21
unnamed: R90.2, T1.24
unnamed: R117.1, U18.3
unnamed: R138.1, R156.1, U50.4
unnamed: R183.2, U1.B15
PG_1V8: J9.F1, U15.6
PORESET_N: R37.1, U1.A17, U19.4
PWR_BTN_N: J1.38, Q5.5
RESET_N: C241.1, D11.2, D13.2, J1.36, J11.6, Q4.1, R45.1, R65.1, R175.2, R186.2, S2.2, U1.C17
UART0_RX: J1.33, R34.1, U1.W14
UART0_TX: J1.35, U1.Y13, U29.2
VAA: C91.2, C92.2, C93.2, C259.2, C260.2, C261.2, C262.2, C263.2, C264.2, C284.2, R163.5, R163.6, R163.7, R163.8, R164.5, R164.6, R164.7, R164.8, R165.5, R165.6, R165.7, R165.8, R166.5, R166.6, R166.7, R166.8, R167.5, R167.6, R167.7, R167.8, R168.5, R168.6, R168.7, R168.8, R169.1, R179.1, R180.1, R181.1, R184.1, U11.3, U11.5
VCCQ: C94.1, C95.1, C96.1, C97.1, C98.1, C99.1, C125.1, R178.2, RS2.4, U1.G7, U1.H6, U1.J7, U1.K6, U1.L7, U1.M6, U1.N7, U1.P6, U1.R7, U1.T6, U1.U7
VD: C17.2, C19.2, C37.2, C39.2, C65.2, C67.2, C69.2, C87.2, C89.2, C90.2, U2.J1, U3.J1, U4.J1, U5.J1, U6.J1, U7.J1, U8.J1, U9.J1, U10.J1, U11.6
VDD: C243.1, C244.1, C245.1, C246.1, C247.1, C248.1, C249.1, C250.1, C251.1, C252.1, C253.1, C254.1, C255.1, C256.1, C257.1, C258.1, RS10.1, U1.AA17, U1.B9, U1.B14, U1.B18, U1.E3, U1.E21, U1.G9, U1.G11, U1.G15, U1.H8, U1.H10, U1.H12, U1.H14, U1.H16, U1.J9, U1.J15, U1.K8, U1.K10, U1.K21, U1.L11, U1.L13, U1.M8, U1.M10, U1.M12, U1.M14, U1.N9, U1.N11, U1.N13, U1.P2, U1.P8, U1.P10, U1.P12, U1.P14, U1.P16, U1.P21, U1.R9, U1.R11, U1.R13, U1.R15, U1.T8, U1.T10, U1.T12, U1.T14, U1.T16, U1.U9, U1.U11, U1.U13, U1.U15, U1.V6, U1.V8, U1.V10, U1.V12, U1.V14, U1.V21, U18.22
VDDA: C105.2, C106.2, C107.2, C112.2, C113.2, U13.12, U13.37, U13.49, U13.64
VDD_COREPLL_N: C207.2, J14.8, RS9.2, U1.K14
VDD_DDRPLL_N: C126.1, J14.14, RS3.1, U1.L9, U1.M9
VDD_DDRPLL_P: C150.1, J14.13, L5.2, RS3.2, RS10.4
VDD_DDR_MEM_N: J14.6, RS1.2
VDD_DDR_MEM_P: J14.5, RS1.3
VDD_DDR_SOC_N: J14.4, RS2.3
VDD_DDR_SOC_P: J14.3, RS2.2
VDD_DDR_VPP_N: C18.2, C20.2, C38.2, C40.2, C240.2, C268.2, C269.2, C270.2, C271.2, C272.2, C273.2, C274.2, C275.2, C276.2, C277.2, C278.2, C279.2, C280.2, RS11.1, U2.B1, U2.M9, U3.B1, U3.M9, U4.B1, U4.M9, U5.B1, U5.M9, U6.B1, U6.M9, U7.B1, U7.M9, U8.B1, U8.M9, U9.B1, U9.M9, U10.B1, U10.M9
VDD_DDR_VPP_P: C281.2, L6.2, R138.2, RS11.2, U50.5
VDD_GEMGXLPLL_N: C129.1, J14.20, RS6.1, U1.K12
VDD_GIVDD_N: C128.1, J14.18, RS5.2, U1.J11
VDD_GIVDD_P: C124.2, C134.2, C135.2, C136.2, C153.1, C155.1, C157.1, C159.1, C161.1, C164.1, C166.2, C168.2, C170.2, C172.2, C174.2, C176.2, C187.2, C188.1, C189.1, C190.1, C191.1, C192.1, C212.2, C215.1, C217.1, D13.1, IC1.22, IC1.28, IC1.39, IC1.44, IC1.49, J1.5, J9.H1, J11.4, J14.9, J14.11, J14.17, L3.2, Q4.2, R12.2, R13.1, R14.1, R15.1, R20.1, R21.1, R22.1, R24.1, R25.1, R37.2, R40.2, R44.2, R45.2, R46.1, R47.1, R48.1, R49.1, R50.1, R51.1, R52.1, R72.2, R98.1, R99.1, R100.1, R101.1, R102.1, R103.1, R104.1, R105.1, R106.1, R107.1, R108.1, R109.1, R110.1, R111.1, R113.2, R114.1, R115.1, R162.1, RS5.1, RS7.2, RS8.2, U12.2, U15.5, U20.1, U21.1, U22.5, U23.1, U24.1, U25.1, U28.5, U29.1, U30.5, U31.5, U32.1, U33.5, U36.3, U36.6, U37.1, U38.5, X1.4, X2.4
VDD_IO_N: C130.1, C131.1, C132.1, C133.1, J14.12, RS7.1, U1.K16, U1.L16, U1.M16, U1.N16
VDD_OTP_N: C206.2, J14.10, RS8.1, U1.G14
VDD_SOC_CORE_N: J14.2, RS10.2
VDD_SOC_CORE_P: J14.1, RS10.3
VMEM: C140.2, C141.2, L4.2, R60.2, RS1.4, RS2.1, U16.16

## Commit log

2018-07-14 Added Freedom U540 DDR and Chiplink
2018-07-14 Изменить 'README.md'
2018-08-14 DDR4_x8_32b_1 updates
2018-08-14 Updated according to the rules of the official KiCAD repo
2018-08-17 Board first draft
2018-09-18 Bom updated
2018-10-02 Updated for 3D
2018-10-04 ki5 board 3D model
2018-10-05 ki5 3D model
2018-10-08 Add STEP file
2018-10-10 .fcstd upload
2018-10-22 Update kicad electric lines
2018-10-29 Part of electric lines model
2018-11-07 Updated .step/.fcstd
2018-11-15 Update lines cpu/memory
2018-12-10 Ki5 update electric lines
2018-12-24 Gerber files for ki5 update
2018-12-31 Gerber update
2019-01-11 Gerber files update
2019-01-20 ki5 update
2019-02-15 Add pic of board
2019-02-15 2019 Copyright
2019-03-06 Gerber updates
2019-03-18 ki5_update
2019-05-07 kicad_update
2019-06-18 Add license files for GPLv3+ and CC by SA 4.0
2019-06-19 Add production spreadsheet, pic of board reverse
2019-06-27 Add pics of cpu reballed
